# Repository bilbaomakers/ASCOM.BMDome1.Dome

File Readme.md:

# ASCOM DOMO BILBAOMAKERS V 1.0.0

Automatizacion de la cupula del Observatorio Astronomico de Marcilla de Campos (Palencia).

Desarrollado por la comunidad Bilbaomakers: https://bilbaomakers.org/ - info@bilbaomakers.org

Desarrollado bajo licencia GNU GENERAL PUBLIC LICENSE Version 3

Descripcion:

Proyecto para desarrollar un controlador para la orientacion Azimut de la cupula del observatorio y el control de la compuerta (Shutter).

Utiliza Arduino como microcontrolador(es) y MQTT como protocolo de comunicaciones entre el PC y el Hardware

Componentes actuales:

- Driver Ascom - MQTT para el control de la cupula desde el PC (Windows) y/o fuente de tracking ( Software, Scope, ....)
- Codigo para el Hardware (Controlador Arduino para el Azimut y controlador para el Shutter).
- Diseño CAD (freecad) de los elementos mecanicos.

04/02/2019 - Proyecto en Desarrollo V 1.0.0 (Branch Development).

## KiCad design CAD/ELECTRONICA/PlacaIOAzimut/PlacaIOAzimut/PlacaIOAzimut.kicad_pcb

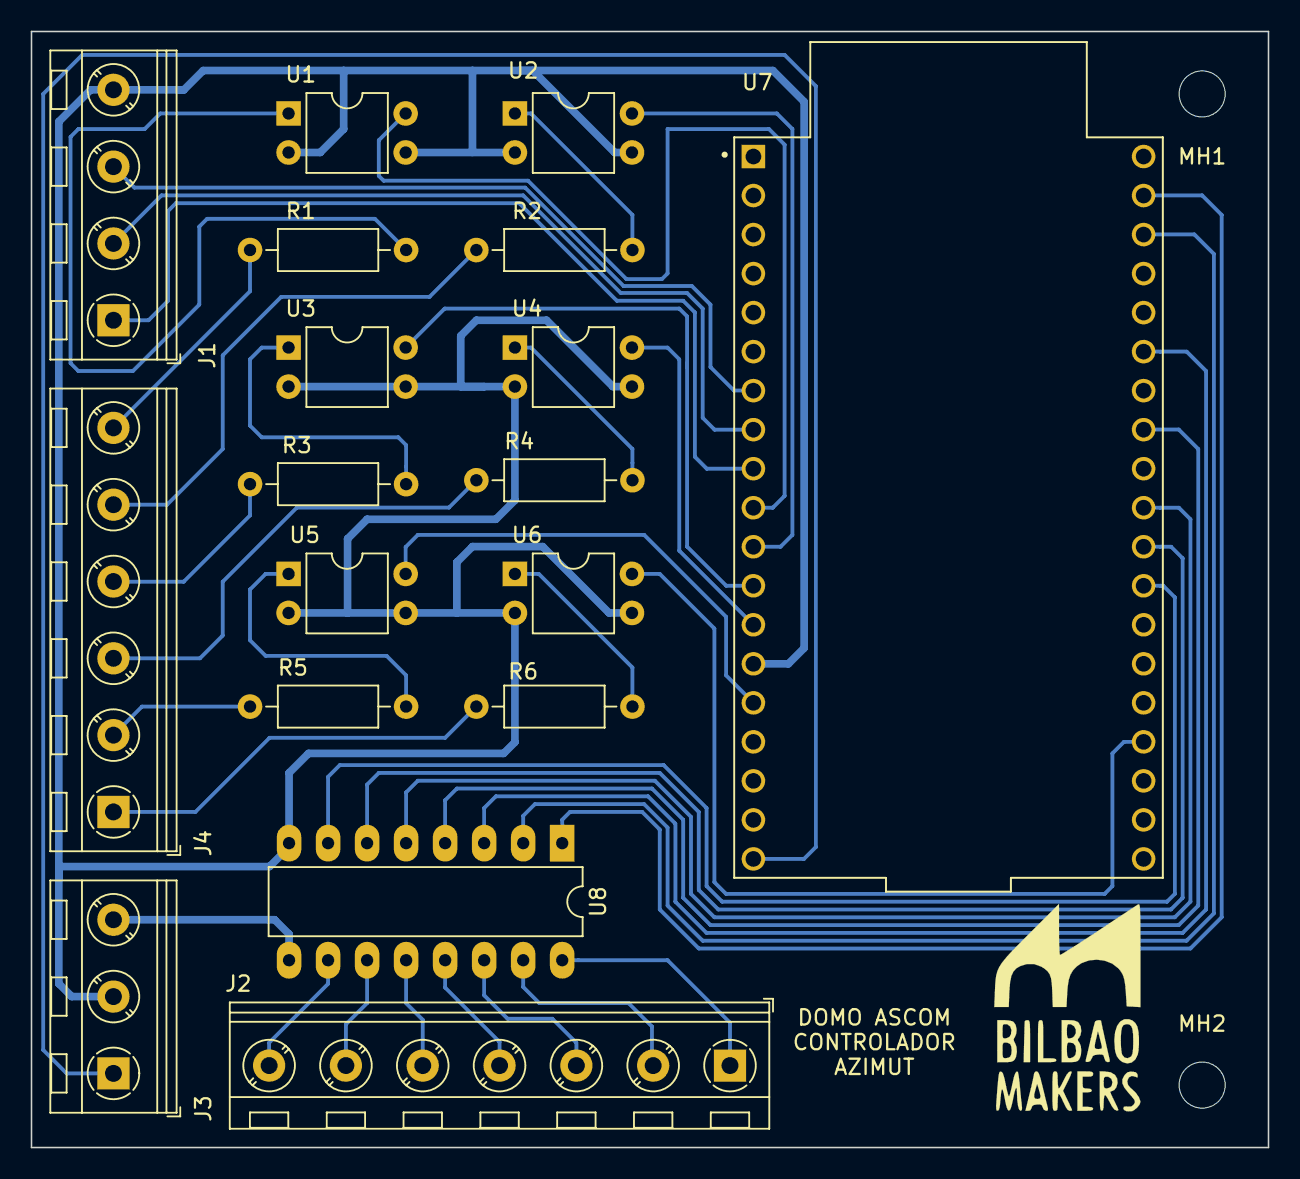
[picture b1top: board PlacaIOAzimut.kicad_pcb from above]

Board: 2 copper layers, 80.5 x 72.6 mm, 20 parts (0 on the bottom side), 38 nets.

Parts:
J1: STEPPER DRV; TerminalBlock_RND_205-00047_1x04_P5.00mm_Horizontal
J2: SALIDAS; TerminalBlock_RND_205-00050_1x07_P5.00mm_Horizontal
J3: POWER SUPP; TerminalBlock_RND_205-00046_1x03_P5.00mm_Horizontal
J4: INPUTS; TerminalBlock_RND_205-00049_1x06_P5.00mm_Horizontal
MH1, MH2: 3mm; MountingHole_3mm
R1, R2, R3, R4, R5, R6: 1K; R_Axial_DIN0207_L6.3mm_D2.5mm_P10.16mm_Horizontal
U1, U2, U3, U4, U5, U6: PC817; DIP-4_W7.62mm
U7: ESP32-DEVKITC; MODULE_ESP32-DEVKITC
U8: ULN2003; DIP-16_W7.62mm_LongPads

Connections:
+5V: J3.1, U7.19
+12V: J3.3, U8.9
GND: J1.4, J3.2, U1.2, U1.3, U2.2, U2.3, U3.2, U3.3, U4.2, U4.3, U5.2, U5.3, U6.2, U6.3, U7.14, U8.8
unnamed: J1.1, U7.9
unnamed: J1.2, U7.8
unnamed: J1.3, U7.7
unnamed: J2.1, U8.16
unnamed: J2.2, U8.15
unnamed: J2.3, U8.14
unnamed: J2.4, U8.13
unnamed: J2.5, U8.12
unnamed: J2.6, U8.11
unnamed: J2.7, U8.10
unnamed: J4.1, R6.2
unnamed: J4.2, R5.2
unnamed: J4.3, R4.2
unnamed: J4.4, R3.2
unnamed: J4.5, R2.2
unnamed: J4.6, R1.2
unnamed: R1.1, U1.1
unnamed: R2.1, U2.1
unnamed: R3.1, U3.1
unnamed: R4.1, U4.1
unnamed: R5.1, U5.1
unnamed: R6.1, U6.1
unnamed: U1.4, U7.10
unnamed: U2.4, U7.11
unnamed: U3.4, U7.12
unnamed: U4.4, U7.13
unnamed: U5.4, U7.15
unnamed: U6.4, U7.23
unnamed: U7.27, U8.7
unnamed: U7.28, U8.6
unnamed: U7.29, U8.5
unnamed: U7.31, U8.4
unnamed: U7.33, U8.3
unnamed: U7.36, U8.2
unnamed: U7.37, U8.1

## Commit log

2019-01-28 Agregar .gitignore y .gitattributes.
2019-01-28 Agregar archivos de proyecto.
2019-01-28 Añadida APP
2019-01-28 Formulario Configuracion
2019-01-28 Create LICENSE
2019-01-28 Acrtualizacion
2019-01-28 Actualizacion
2019-01-28 Actualizado a Framework 4.5.2 para compatibilidad con libreria MQTT
2019-01-28 Conexion con Mosquitto
2019-01-30 Actualizado Salvar Configuracion con Ascom Profile
2019-01-31 Iniciado Codigo de Arduino para ESP-12E
2019-02-01 Actualizaciones
2019-02-04 Incluido codigo Arduino para control Shutter
2019-02-04 Pruebas
2019-02-04 Nueva Rama
2019-02-04 Test
2019-02-04 Cambio PC
2019-02-04 Peleando con MQTT
2019-02-05 Doc de comunicaciones
2019-02-05 MQTT Arduino
2019-02-06 Prueba1
2019-02-07 HW Azimut base de comunicaciones OK
2019-02-07 Determinar una version unica para el CAD ( Freecad )
2019-02-07 Peleando con JSON
2019-02-11 Añadidos comandos via Serie para configuracion de Wifi y MQTT
2019-02-11 Mejorada la gestion de la WIFI. Añadido gestion por linea de comandos via puerto serie. Comando WIFI. Añadidos comandos via Serie para gestion de la conexion MQTT
2019-02-11 Implementando Clase BMDomo1
2019-02-19 Create basura
2019-02-20 Actualizacion documentacion comunicaciones
2019-02-21 Ordenar el codigo. Comunicaciones OK. Gestion de LWT OK y probada. Comandos via Serie. Actualizacion de DOC
2019-02-21 Arreglillos
2019-02-21 Currelo a saco
2019-02-22 Trabajando en el Objeto Cupula en Arduino
2019-02-26 Currando con el objeto BMDome1
2019-03-01 Trabajando en la clase BMDomo1
2019-03-07 Mas currelo. Afinando el MoveTo y añadido algun comando mas.
2019-03-09 Funcion GOTO
2019-03-14 Stepper
2019-03-20 Funcion GOTO OK
2019-03-21 ajustes
2019-03-22 Adaptando a ESP32 y libreria WiFiMQTTManager
2019-03-25 Reorganizacion del proyecto
2019-03-25 Borrar lo de Visual Studio
2019-03-25 Proyecto migrado a ESP32 y Visual Code Platform IO
2019-03-25 Adaptando a ESP32 y Platform.IO
2019-03-27 Adaptado a PlatformIO. Trabajando en las Tasks
2019-03-29 Ajustando el lio MQTT (Strings y c_str)
2019-04-01 Nuevas Lib OK.
2019-04-01 Ajuste de Tareas
2019-04-01 Mejorar onMqttMessage
2019-04-02 Arreglos
2019-04-02 Librerias
2019-04-02 Fotos
2019-04-04 AsyncMQTT y Cores
2019-04-05 tasks
2019-04-05 Tareas
2019-04-05 Task Bastante OK. Implementar Colas.
2019-04-05 Implementando Colas MQTT
2019-04-07 Colas
2019-04-09 Tareas. Problemas de InstrFetchProhibited
2019-04-10 Comunicaciones OK por colas.
2019-04-10 Mejoras
2019-04-12 Mejorando control Stepper
2019-04-15 Core1 para Stepper
2019-04-15 Cambiar los comandos serie
2019-04-16 Upload
2019-04-17 Estable
2019-04-17 Actualizacion Motores
2019-04-17 Golpe motor casi quitado del todo
2019-04-23 Versión del código de Azimut al que le he añadido la parte del shutter (compuerta)
2019-04-25 Caja Electrica 1
2019-05-08 Libreria
2019-05-15 Pre Adapar Libreria
2019-05-15 Pre Adaptar Lib Stepper
2019-05-23 Libreria Accelstepper ESP32 Timer
2019-05-23 Tele 1s
2019-05-27 Motor OK
2019-05-27 Implementando Comandos
2019-05-29 Mas Comandos
2019-05-31 Unificadas comunicaciones MQTT y Serial
2019-05-31 Eliminada Libreria SerialCommands
2019-06-25 Reloj NTP y config de sensores para HomeAssistant
2019-07-08 DXF Files
2019-07-11 Mando M5Stack
2019-07-11 Logo
2019-10-22 CAD Version 3
2019-10-23 Actualizacion CAD
2019-10-23 DXF varios
2019-10-28 3 tornillos mas en lateral base motor
2019-10-30 Orden
2019-11-07 Mecanizado
2019-11-08 Subir
2022-04-21 Placa Azimut
2022-04-21 Software Update
2022-05-20 CAD Placa, fabricacion PCBWay
2022-05-20 Implementando Gestion Cuadro Mando
2022-06-30 Pruebas Cuandromando 1
2022-06-30 Arreglando Botones
2022-07-01 Test Botones
2022-07-02 Slew Relative Ajuste
2022-07-05 Prueba Botones lio instancias
2022-07-05 Quitar Clase Cuadromando
2022-07-06 Quitando Clase Cuadromando
2022-07-06 Botones OK. quitar clase BMDOMO
2022-07-07 Desclaseando. Hacer bien las predeclaraciones.
2022-07-13 Test GIT
2022-07-13 Quitar Clases Paso 1 Compila
2022-07-13 Probar y repasar findhome
2022-07-13 V1b1 INSTALADOR PROBADA
2022-07-14 Haciendo Nueva Maquina Estado.
2022-07-30 Tapa Rodamiento V2
2022-07-30 Tapa Rodamiento V2 CAM
2022-07-30 Tapa rodamiento cam fresa 4mm
